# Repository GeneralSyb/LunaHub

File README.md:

# LunaHub
Astronomy power and USB hub, in development.

For now just work in progress design files for the USB hub PCB. On top of this will come the power supply PCB that has a number of buck converters to power the USB hub and a handfull of barrel jacks. I chose to keep these two boards seperate so that I don't need to worry too much about keeping one PCB small and so that I can build and test them indepentendly. To provide power to the USB hub the PSU board has a 1.1V and a 3.3V buck converter which can supply enough current to power all the electronics. The example design from TI for the TUSB8041 USB 3.1 hub IC show the usage of load switches which are controller by the IC to switch the maximum current as requested by the connected device. However to save on cost and to allow "dumb" devices to draw a lot of current, I didn't do this and connected the USB 5V power pins directly to the buck converters on the PSU board. Of course with a poly fuse chosen to allow a maximum current of 1.5A per port.

I chose to use the TUSB8041 hub IC because it was cheap, provides a lot of automatic features and seemed easy enough to use in a DIY USB hub, given my experience (which honestly isn't a whole lot).
For configuration of the IC there are a number for pins that are pulled either high or low with a resistor, and the rest is done by programming the I2C EEPROM IC. This storage chip can be programmed by removing the jumpers and connecting GND, 3.3V, SDA and SCL to an external microcontroller. The minimum amount of EEPROM storage required by the TUSB8041 is 2kB, so the 4kB EEPROM IC that I chose should be plenty.

All the differential pair lines and vias should have an impedance of 90 Ohms with a tolerance of 5% and the superspeed lines have their length matched as best as possible. The highspeed lines are mostly the same, except for the upstream port where the placement of the pins on the connector made the length matching really hard. This has been calculated using the Saturn PCB toolkit with a dielectric constant of 4.1 and a prepreg thickness on the 0.0994mm. (more details about the JLC04161H-3313 stackup can be found on [JLCPCB's](https://jlcpcb.com/impedance) website)

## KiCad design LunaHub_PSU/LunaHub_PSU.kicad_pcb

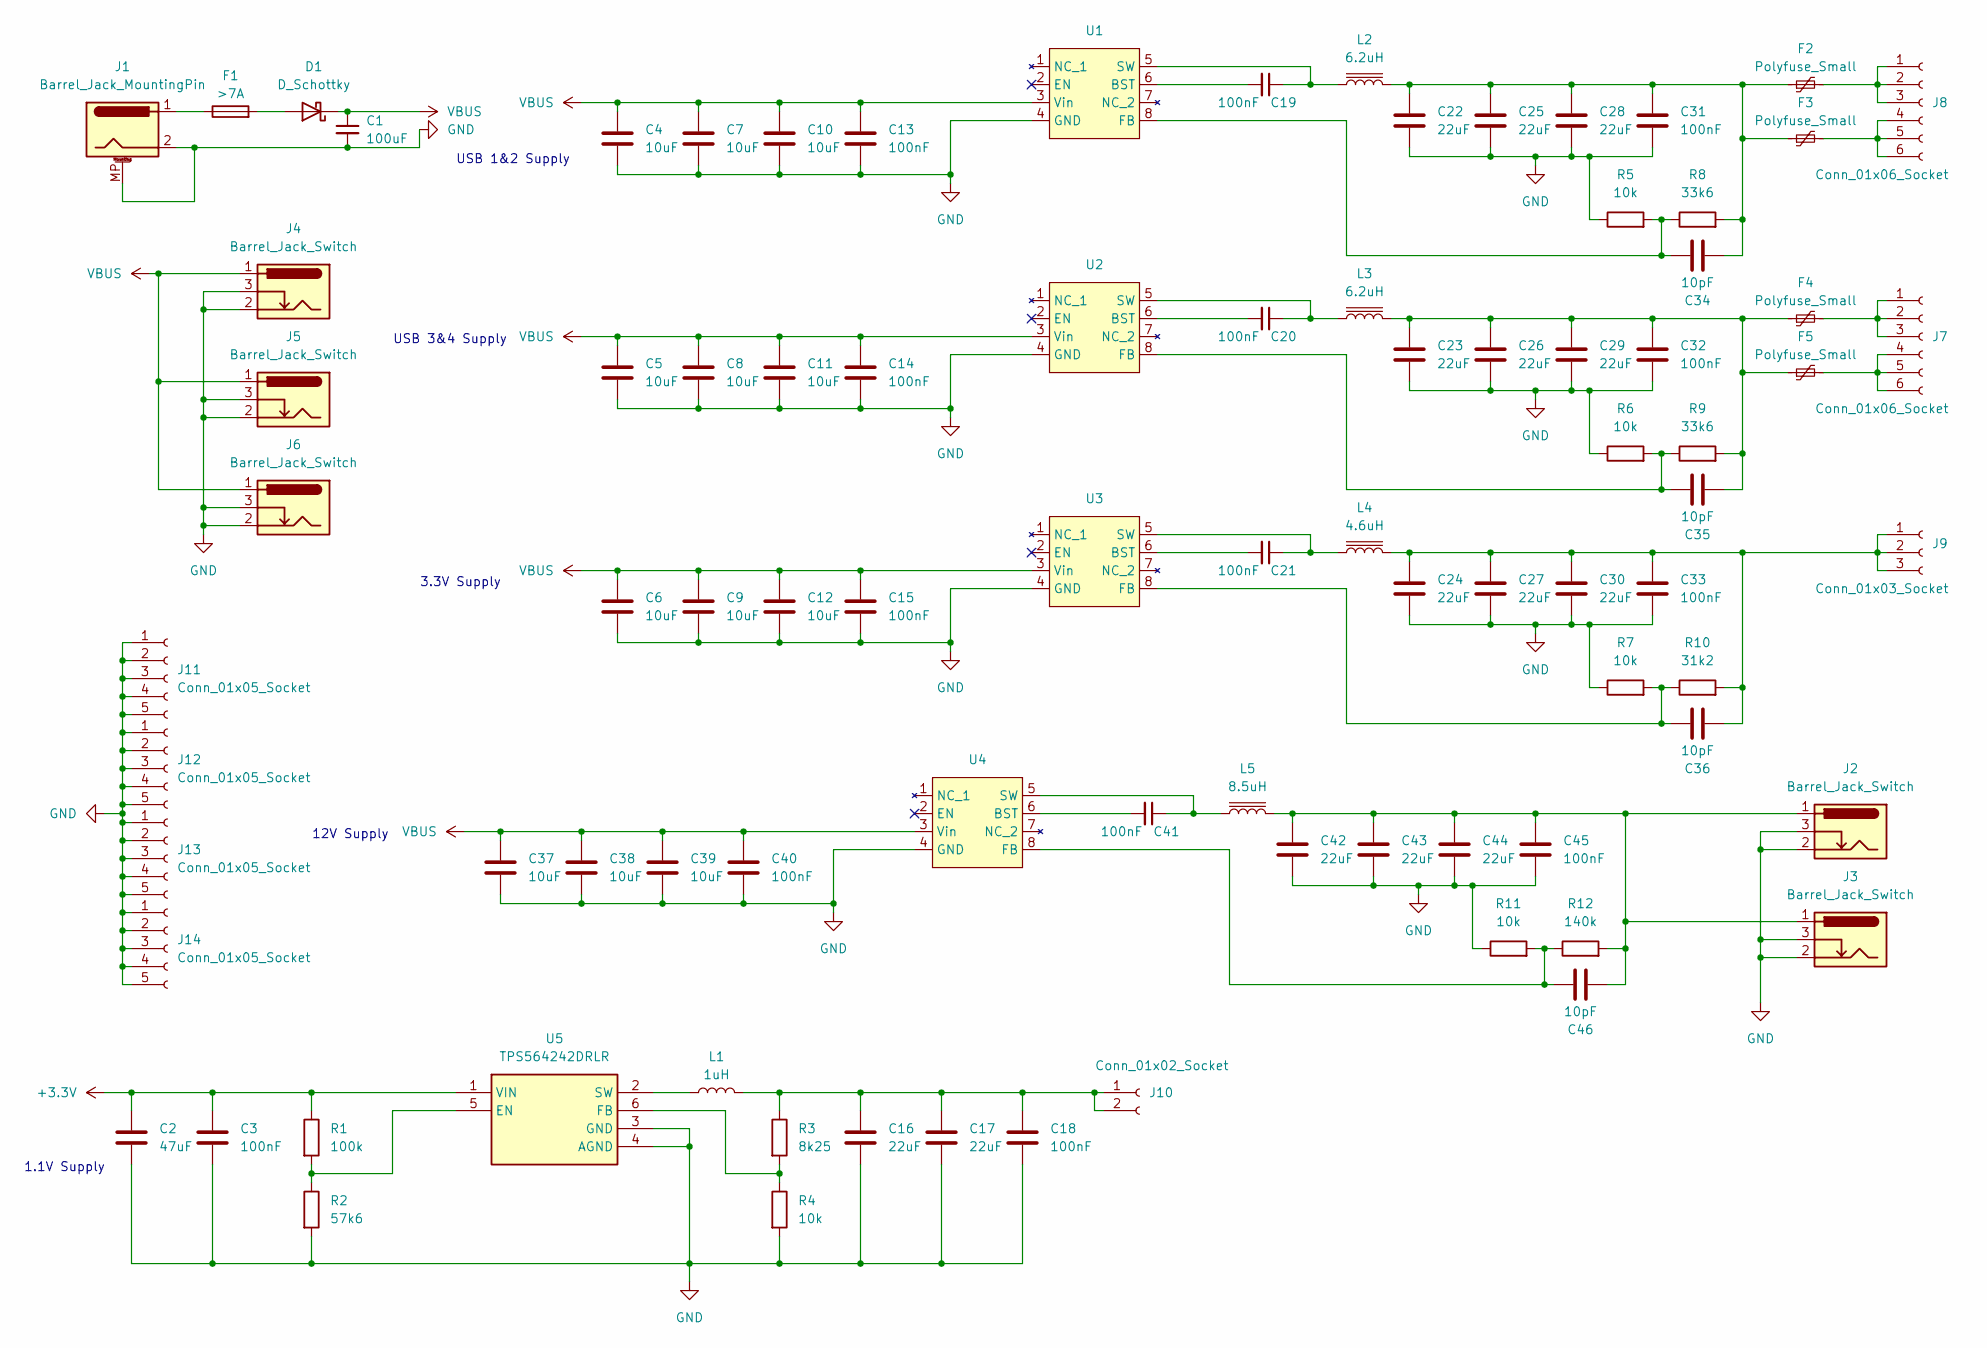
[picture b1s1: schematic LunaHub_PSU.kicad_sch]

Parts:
C1: 100uF; CP_Radial_D10.0mm_P2.50mm_P5.00mm
C2: 47uF; C_1210_3225Metric
C3, C13, C14, C15, C18, C19, C20, C21, C31, C32, C33, C40, C41, C45: 100nF; C_0805_2012Metric
C4, C5, C6, C7, C8, C9, C10, C11, C12, C37, C38, C39: 10uF; C_0805_2012Metric
C16, C17, C22, C23, C24, C25, C26, C27, C28, C29, C30, C42, C43, C44: 22uF; C_1210_3225Metric
C34, C35, C36, C46: 10pF; C_0402_1005Metric
D1: D_Schottky; D_PowerDI-5
F1: >7A; Fuseholder_Cylinder-5x20mm_Schurter_0031_8201_Horizontal_Op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
F2: Polyfuse_Small; Fuse_1206_3216Metric
F3, F4, F5: Polyfuse_Small; Fuse_0805_2012Metric
J1: Barrel_Jack_MountingPin; PJ082BH
J2, J3, J4, J5, J6: Barrel_Jack_Switch; BarrelJack_Wuerth_6941xx301002
J7, J8: Conn_01x06_Socket; PinHeader_1x06_P2.54mm_Vertical
J9: Conn_01x03_Socket; PinHeader_1x03_P2.54mm_Vertical
J10: Conn_01x02_Socket; PinHeader_1x02_P2.54mm_Vertical
J11, J12, J13, J14: Conn_01x05_Socket; PinHeader_1x05_P2.54mm_Vertical
L1: 1uH; L_1008_2520Metric
L2, L3: 6.2uH; L_Bourns_SRP7028A_7.3x6.6mm
L4: 4.6uH; L_Bourns_SRP7028A_7.3x6.6mm
L5: 8.5uH; L_Bourns_SRP7028A_7.3x6.6mm
R1: 100k; R_0805_2012Metric
R2: 57k6; R_0805_2012Metric
R3: 8k25; R_0805_2012Metric
R4: 10k; R_0805_2012Metric
R5, R6, R7, R11: 10k; R_0603_1608Metric
R8, R9: 33k6; R_0603_1608Metric
R10: 31k2; R_0603_1608Metric
R12: 140k; R_0603_1608Metric
U1, U2, U3, U4: SOT-583-8
U5: TPS564242DRLR; SOTFL50P160X60-6N; Mouser Part Number 595-TPS564242DRLR

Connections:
+3.3V: C2.1, C3.1, R1.1, U5.1 (VIN)
GND: C1.2, C2.2, C3.2, C4.2, C5.2, C6.2, C7.2, C8.2, C9.2, C10.2, C11.2, C12.2, C13.2, C14.2, C15.2, C16.2, C17.2, C18.2, C22.2, C23.2, C24.2, C25.2, C26.2, C27.2, C28.2, C29.2, C30.2, C31.2, C32.2, C33.2, C37.2, C38.2, C39.2, C40.2, C42.2, C43.2, C44.2, C45.2, J1.2, J1.MP (MountPin), J2.2, J2.3, J3.2, J3.3, J4.2, J4.3, J5.2, J5.3, J6.2, J6.3, J11.1, J11.2, J11.3, J11.4, J11.5, J12.1, J12.2, J12.3, J12.4, J12.5, J13.1, J13.2, J13.3, J13.4, J13.5, J14.1, J14.2, J14.3, J14.4, J14.5, R2.2, R4.2, R5.1, R6.1, R7.1, R11.1, U1.4 (GND), U2.4 (GND), U3.4 (GND), U4.4 (GND), U5.3 (GND), U5.4 (AGND)
unnamed: C22.1, C25.1, C28.1, C31.1, C34.2, F2.1, F3.1, L2.2, R8.2
unnamed: C23.1, C26.1, C29.1, C32.1, C35.2, F4.1, F5.1, L3.2, R9.2
unnamed: C42.1, C43.1, C44.1, C45.1, C46.2, J2.1, J3.1, L5.2, R12.2
unnamed: D1.2 (A), F1.2
unnamed: F1.1, J1.1
unnamed: F4.2, J7.1, J7.2, J7.3
unnamed: F5.2, J7.4, J7.5, J7.6
unnamed: F2.2, J8.1, J8.2, J8.3
unnamed: F3.2, J8.4, J8.5, J8.6
unnamed: C24.1, C27.1, C30.1, C33.1, C36.2, J9.1, J9.2, J9.3, L4.2, R10.2
unnamed: C16.1, C17.1, C18.1, J10.1, J10.2, L1.2, R3.1
unnamed: C19.2, U1.6 (BST)
unnamed: C34.1, R5.2, R8.1, U1.8 (FB)
unnamed: C19.1, L2.1, U1.5 (SW)
unnamed: C20.2, U2.6 (BST)
unnamed: C35.1, R6.2, R9.1, U2.8 (FB)
unnamed: C20.1, L3.1, U2.5 (SW)
unnamed: C21.2, U3.6 (BST)
unnamed: C36.1, R7.2, R10.1, U3.8 (FB)
unnamed: C21.1, L4.1, U3.5 (SW)
unnamed: C41.2, U4.6 (BST)
unnamed: C46.1, R11.2, R12.1, U4.8 (FB)
unnamed: C41.1, L5.1, U4.5 (SW)
unnamed: R1.2, R2.1, U5.5 (EN)
unnamed: R3.2, R4.1, U5.6 (FB)
unnamed: L1.1, U5.2 (SW)
VBUS: C1.1, C4.1, C5.1, C6.1, C7.1, C8.1, C9.1, C10.1, C11.1, C12.1, C13.1, C14.1, C15.1, C37.1, C38.1, C39.1, C40.1, D1.1 (K), J4.1, J5.1, J6.1, U1.3 (Vin), U2.3 (Vin), U3.3 (Vin), U4.3 (Vin)

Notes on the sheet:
USB 1&2 Supply
1.1V Supply
3.3V Supply
12V Supply
USB 3&4 Supply

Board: 2 copper layers, 88 parts (0 on the bottom side), 29 nets, no tracks yet.

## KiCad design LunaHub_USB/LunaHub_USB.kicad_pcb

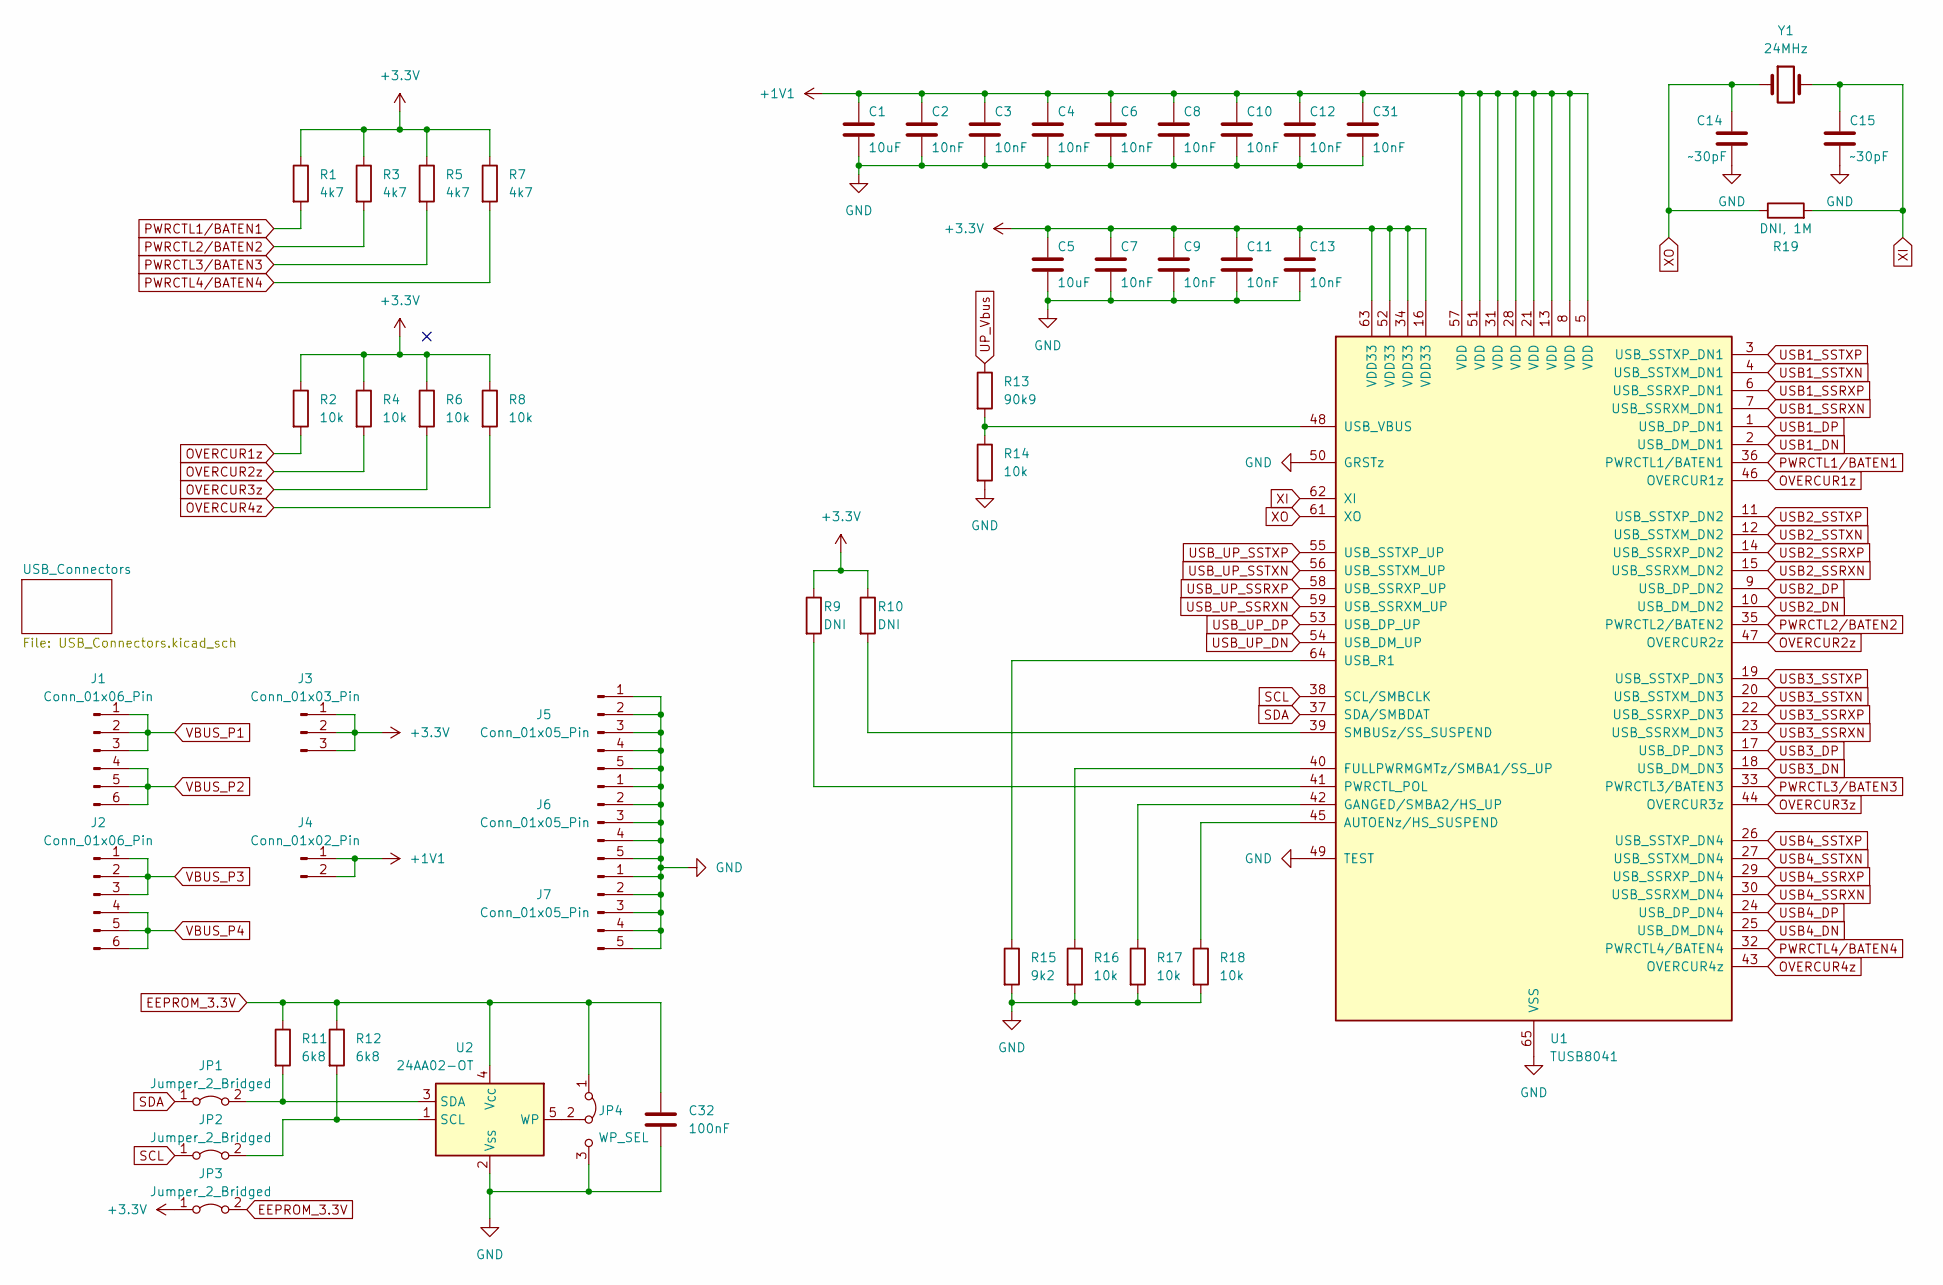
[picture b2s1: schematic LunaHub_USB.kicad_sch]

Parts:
C1, C5: 10uF; C_0805_2012Metric
C2, C3, C4, C6, C7, C8, C9, C10, C11, C12, C13, C31: 10nF; C_0402_1005Metric
C14, C15: ~30pF; C_0402_1005Metric
C32: 100nF; C_0402_1005Metric
J1, J2: Conn_01x06_Pin; PinHeader_1x06_P2.54mm_Vertical
J3: Conn_01x03_Pin; PinHeader_1x03_P2.54mm_Vertical
J4: Conn_01x02_Pin; PinHeader_1x02_P2.54mm_Vertical
J5, J6, J7: Conn_01x05_Pin; PinHeader_1x05_P2.54mm_Vertical
JP1, JP2, JP3: Jumper_2_Bridged; PinHeader_1x02_P2.54mm_Vertical
JP4: WP_SEL; PinHeader_1x03_P2.54mm_Vertical
R1, R3, R5, R7: 4k7; R_0402_1005Metric
R2, R4, R6, R8, R14, R16, R17, R18: 10k; R_0402_1005Metric
R9, R10: DNI; R_0402_1005Metric
R11, R12: 6k8; R_0402_1005Metric
R13: 90k9; R_0402_1005Metric
R15: 9k2; R_0402_1005Metric
R19: DNI, 1M; R_0402_1005Metric
U1: TUSB8041; QFN-64-1EP_9x9mm_P0.5mm_EP6x6mm_ThermalVias
U2: 24AA02-OT; SOT-23-5
Y1: 24MHz; Crystal_HC49-4H_Vertical

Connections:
+1V1: C1.1, C2.1, C3.1, C4.1, C6.1, C8.1, C10.1, C12.1, C31.1, J4.1, J4.2, U1.5 (VDD), U1.8 (VDD), U1.13 (VDD), U1.21 (VDD), U1.28 (VDD), U1.31 (VDD), U1.51 (VDD), U1.57 (VDD)
+3.3V: C5.1, C7.1, C9.1, C11.1, C13.1, J3.1, J3.2, J3.3, JP3.1 (A), R1.1, R2.1, R3.1, R4.1, R5.1, R6.1, R7.1, R8.1, R9.1, R10.1, U1.16 (VDD33), U1.34 (VDD33), U1.52 (VDD33), U1.63 (VDD33)
EEPROM_3.3V: C32.1, JP3.2 (B), JP4.1 (A), R11.1, R12.1, U2.4 (V_{CC})
GND: C1.2, C2.2, C3.2, C4.2, C5.2, C6.2, C7.2, C8.2, C9.2, C10.2, C11.2, C12.2, C13.2, C14.2, C15.2, C31.2, C32.2, J5.1, J5.2, J5.3, J5.4, J5.5, J6.1, J6.2, J6.3, J6.4, J6.5, J7.1, J7.2, J7.3, J7.4, J7.5, JP4.3 (B), R14.2, R15.2, R16.2, R17.2, R18.2, U1.49 (TEST), U1.50 (GRSTz), U1.65 (VSS), U2.2 (V_{SS}); also elsewhere on the board
unnamed: JP1.2 (B), R11.2, U2.3 (SDA)
unnamed: JP2.2 (B), R12.2, U2.1 (SCL)
unnamed: JP4.2 (C), U2.5 (WP)
unnamed: R18.1, U1.45 (AUTOENz/HS_SUSPEND)
unnamed: R16.1, U1.40 (FULLPWRMGMTz/SMBA1/SS_UP)
unnamed: R17.1, U1.42 (GANGED/SMBA2/HS_UP)
unnamed: R9.2, U1.41 (PWRCTL_POL)
unnamed: R10.2, U1.39 (SMBUSz/SS_SUSPEND)
unnamed: R15.1, U1.64 (USB_R1)
unnamed: R13.2, R14.1, U1.48 (USB_VBUS)
OVERCUR1z: R2.2, U1.46 (OVERCUR1z)
OVERCUR2z: R4.2, U1.47 (OVERCUR2z)
OVERCUR3z: R6.2, U1.44 (OVERCUR3z)
OVERCUR4z: R8.2, U1.43 (OVERCUR4z)
PWRCTL1/BATEN1: R1.2, U1.36 (PWRCTL1/BATEN1)
PWRCTL2/BATEN2: R3.2, U1.35 (PWRCTL2/BATEN2)
PWRCTL3/BATEN3: R5.2, U1.33 (PWRCTL3/BATEN3)
PWRCTL4/BATEN4: R7.2, U1.32 (PWRCTL4/BATEN4)
SCL: JP2.1 (A), U1.38 (SCL/SMBCLK)
SDA: JP1.1 (A), U1.37 (SDA/SMBDAT)
UP_Vbus: R13.1; also elsewhere on the board
USB1_DN: U1.2 (USB_DM_DN1); also elsewhere on the board
USB1_DP: U1.1 (USB_DP_DN1); also elsewhere on the board
USB1_SSRXN: U1.7 (USB_SSRXM_DN1); also elsewhere on the board
USB1_SSRXP: U1.6 (USB_SSRXP_DN1); also elsewhere on the board
USB1_SSTXN: U1.4 (USB_SSTXM_DN1); also elsewhere on the board
USB1_SSTXP: U1.3 (USB_SSTXP_DN1); also elsewhere on the board
USB2_DN: U1.10 (USB_DM_DN2); also elsewhere on the board
USB2_DP: U1.9 (USB_DP_DN2); also elsewhere on the board
USB2_SSRXN: U1.15 (USB_SSRXM_DN2); also elsewhere on the board
USB2_SSRXP: U1.14 (USB_SSRXP_DN2); also elsewhere on the board
USB2_SSTXN: U1.12 (USB_SSTXM_DN2); also elsewhere on the board
USB2_SSTXP: U1.11 (USB_SSTXP_DN2); also elsewhere on the board
USB3_DN: U1.18 (USB_DM_DN3); also elsewhere on the board
USB3_DP: U1.17 (USB_DP_DN3); also elsewhere on the board
USB3_SSRXN: U1.23 (USB_SSRXM_DN3); also elsewhere on the board
USB3_SSRXP: U1.22 (USB_SSRXP_DN3); also elsewhere on the board
USB3_SSTXN: U1.20 (USB_SSTXM_DN3); also elsewhere on the board
USB3_SSTXP: U1.19 (USB_SSTXP_DN3); also elsewhere on the board
USB4_DN: U1.25 (USB_DM_DN4); also elsewhere on the board
USB4_DP: U1.24 (USB_DP_DN4); also elsewhere on the board
USB4_SSRXN: U1.30 (USB_SSRXM_DN4); also elsewhere on the board
USB4_SSRXP: U1.29 (USB_SSRXP_DN4); also elsewhere on the board
USB4_SSTXN: U1.27 (USB_SSTXM_DN4); also elsewhere on the board
USB4_SSTXP: U1.26 (USB_SSTXP_DN4); also elsewhere on the board
USB_UP_DN: U1.54 (USB_DM_UP); also elsewhere on the board
USB_UP_DP: U1.53 (USB_DP_UP); also elsewhere on the board
USB_UP_SSRXN: U1.59 (USB_SSRXM_UP); also elsewhere on the board
USB_UP_SSRXP: U1.58 (USB_SSRXP_UP); also elsewhere on the board
USB_UP_SSTXN: U1.56 (USB_SSTXM_UP); also elsewhere on the board
USB_UP_SSTXP: U1.55 (USB_SSTXP_UP); also elsewhere on the board
VBUS_P1: J1.1, J1.2, J1.3; also elsewhere on the board
VBUS_P2: J1.4, J1.5, J1.6; also elsewhere on the board
VBUS_P3: J2.1, J2.2, J2.3; also elsewhere on the board
VBUS_P4: J2.4, J2.5, J2.6; also elsewhere on the board
XI: C15.1, R19.2, U1.62 (XI), Y1.2
XO: C14.1, R19.1, U1.61 (XO), Y1.1

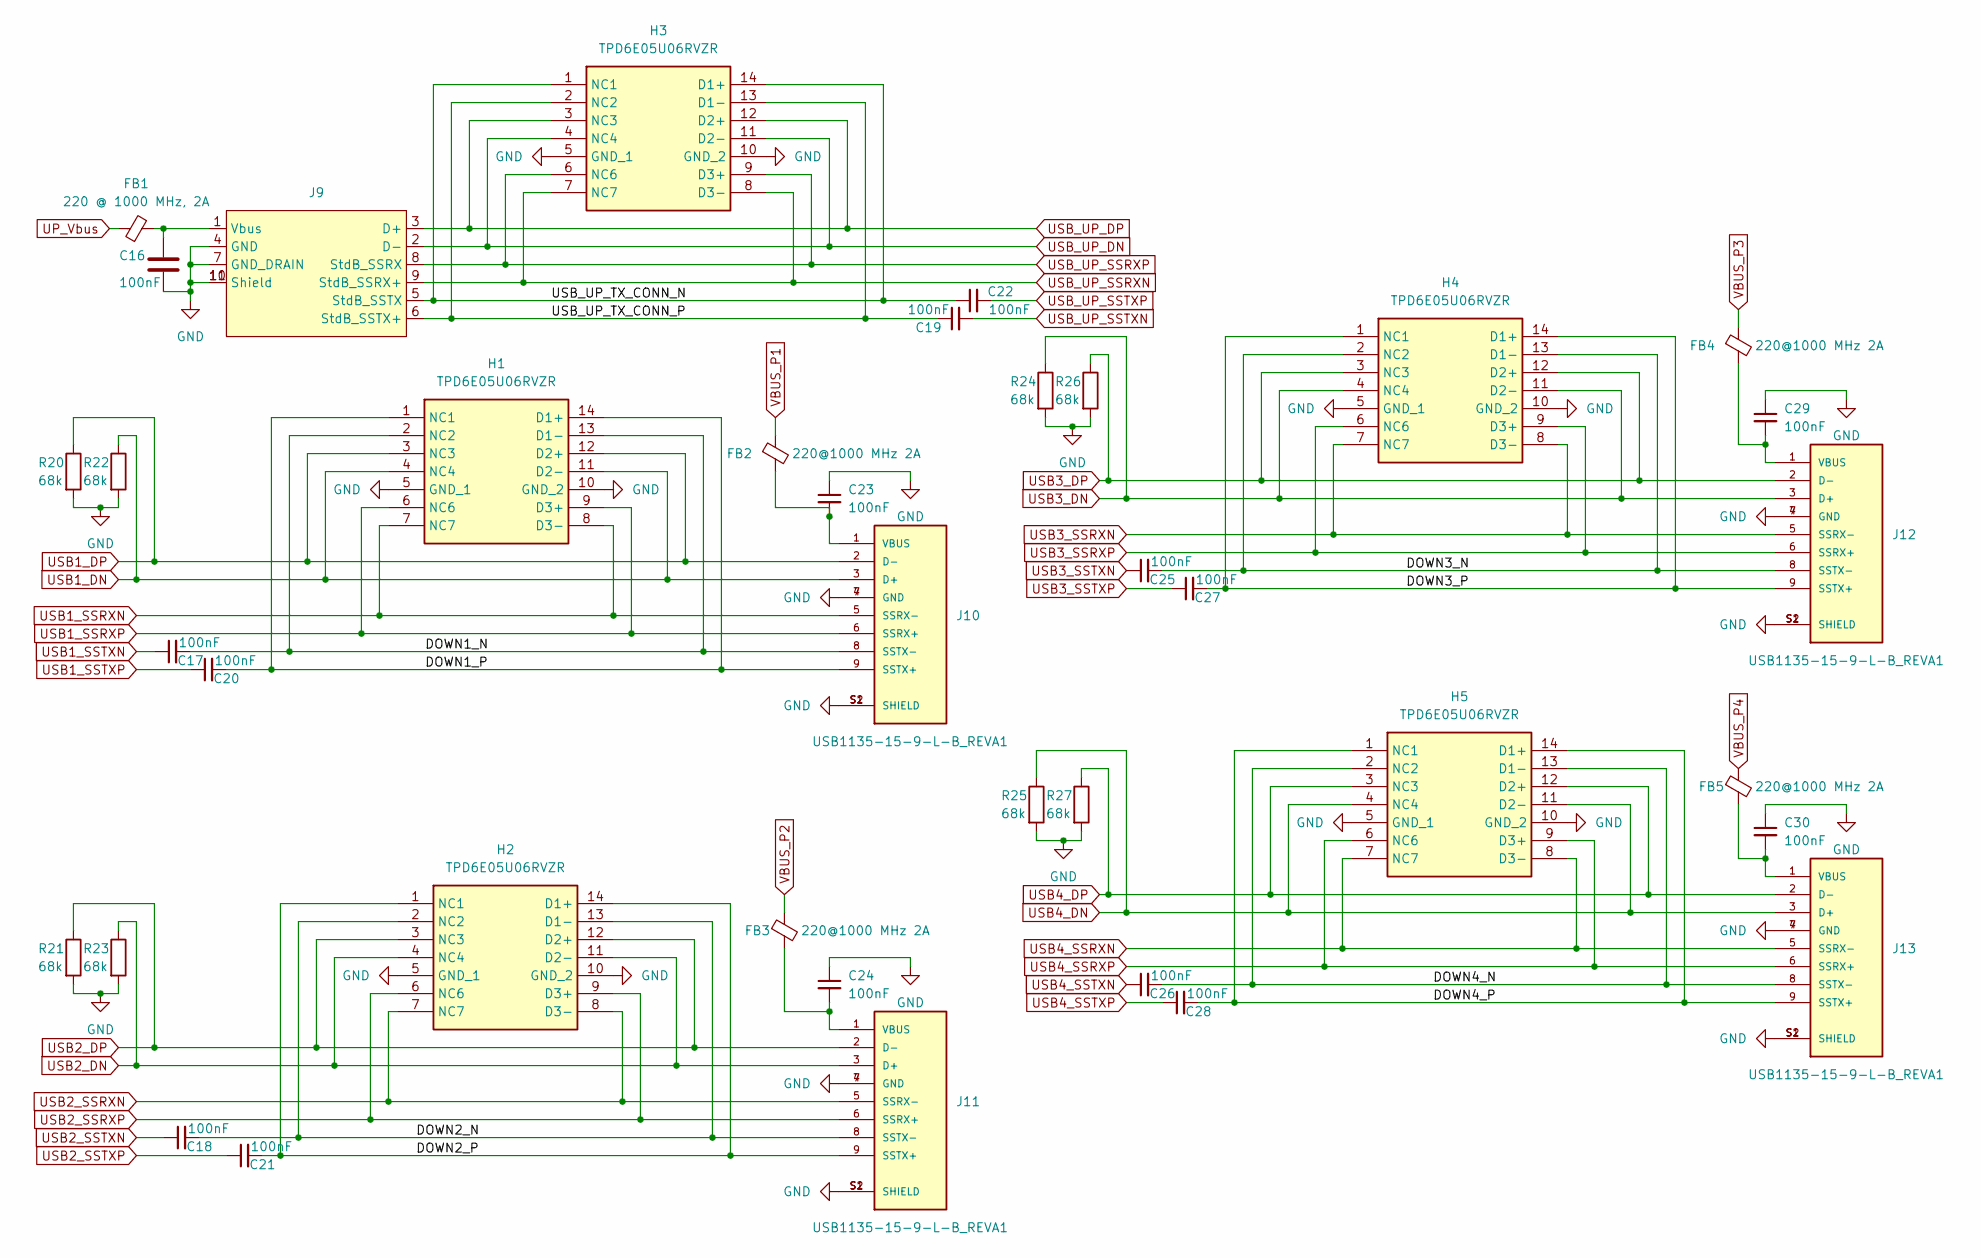
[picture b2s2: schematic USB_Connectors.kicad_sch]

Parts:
C16, C17, C18, C19, C20, C21, C22, C23, C24, C25, C26, C27, C28, C29, C30: 100nF; C_0402_1005Metric
FB1: 220 @ 1000 MHz, 2A; R_1206_3216Metric
FB2, FB3, FB4, FB5: 220@1000 MHz 2A; R_1206_3216Metric
H1, H2, H3, H4, H5: TPD6E05U06RVZR; SON50P135X350X55-14N; Mouser Part Number 595-TPD6E05U06RVZR
J9: WR-COM_USB_TYPE_B
J10, J11, J12, J13: USB1135-15-9-L-B_REVA1; GCT_USB1135-15-9-L-B_REVA1; PARTREV A1; DigiKey_Part_Number 2073-USB1135-15-9-L-B-ND
R20, R21, R22, R23, R24, R25, R26, R27: 68k; R_0402_1005Metric

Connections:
/USB_Connectors/DOWN1_N: C17.2, H1.2 (NC2), H1.13 (D1-), J10.8 (SSTX-)
/USB_Connectors/DOWN1_P: C20.2, H1.1 (NC1), H1.14 (D1+), J10.9 (SSTX+)
/USB_Connectors/DOWN2_N: C18.2, H2.2 (NC2), H2.13 (D1-), J11.8 (SSTX-)
/USB_Connectors/DOWN2_P: C21.2, H2.1 (NC1), H2.14 (D1+), J11.9 (SSTX+)
/USB_Connectors/DOWN3_N: C25.2, H4.2 (NC2), H4.13 (D1-), J12.8 (SSTX-)
/USB_Connectors/DOWN3_P: C27.2, H4.1 (NC1), H4.14 (D1+), J12.9 (SSTX+)
/USB_Connectors/DOWN4_N: C26.2, H5.2 (NC2), H5.13 (D1-), J13.8 (SSTX-)
/USB_Connectors/DOWN4_P: C28.2, H5.1 (NC1), H5.14 (D1+), J13.9 (SSTX+)
/USB_Connectors/USB_UP_TX_CONN_N: C22.1, H3.1 (NC1), H3.14 (D1+), J9.5 (StdB_SSTX)
/USB_Connectors/USB_UP_TX_CONN_P: C19.1, H3.2 (NC2), H3.13 (D1-), J9.6 (StdB_SSTX+)
GND: C16.2, C23.1, C24.1, C29.1, C30.1, H1.5 (GND_1), H1.10 (GND_2), H2.5 (GND_1), H2.10 (GND_2), H3.5 (GND_1), H3.10 (GND_2), H4.5 (GND_1), H4.10 (GND_2), H5.5 (GND_1), H5.10 (GND_2), J9.4 (GND), J9.7 (GND_DRAIN), J9.10 (Shield), J9.11 (Shield), J10.4 (GND), J10.7 (GND), J10.S1 (SHIELD), J10.S2 (SHIELD), J11.4 (GND), J11.7 (GND), J11.S1 (SHIELD), J11.S2 (SHIELD), J12.4 (GND), J12.7 (GND), J12.S1 (SHIELD), J12.S2 (SHIELD), J13.4 (GND), J13.7 (GND), J13.S1 (SHIELD), J13.S2 (SHIELD), R20.2, R21.2, R22.2, R23.2, R24.2, R25.2, R26.2, R27.2; also elsewhere on the board
unnamed: C16.1, FB1.2, J9.1 (Vbus)
unnamed: C23.2, FB2.2, J10.1 (VBUS)
unnamed: C24.2, FB3.2, J11.1 (VBUS)
unnamed: C29.2, FB4.2, J12.1 (VBUS)
unnamed: C30.2, FB5.2, J13.1 (VBUS)
UP_Vbus: FB1.1; also elsewhere on the board
USB1_DN: H1.4 (NC4), H1.11 (D2-), J10.3 (D+), R22.1; also elsewhere on the board
USB1_DP: H1.3 (NC3), H1.12 (D2+), J10.2 (D-), R20.1; also elsewhere on the board
USB1_SSRXN: H1.7 (NC7), H1.8 (D3-), J10.5 (SSRX-); also elsewhere on the board
USB1_SSRXP: H1.6 (NC6), H1.9 (D3+), J10.6 (SSRX+); also elsewhere on the board
USB1_SSTXN: C17.1; also elsewhere on the board
USB1_SSTXP: C20.1; also elsewhere on the board
USB2_DN: H2.4 (NC4), H2.11 (D2-), J11.3 (D+), R23.1; also elsewhere on the board
USB2_DP: H2.3 (NC3), H2.12 (D2+), J11.2 (D-), R21.1; also elsewhere on the board
USB2_SSRXN: H2.7 (NC7), H2.8 (D3-), J11.5 (SSRX-); also elsewhere on the board
USB2_SSRXP: H2.6 (NC6), H2.9 (D3+), J11.6 (SSRX+); also elsewhere on the board
USB2_SSTXN: C18.1; also elsewhere on the board
USB2_SSTXP: C21.1; also elsewhere on the board
USB3_DN: H4.4 (NC4), H4.11 (D2-), J12.3 (D+), R24.1; also elsewhere on the board
USB3_DP: H4.3 (NC3), H4.12 (D2+), J12.2 (D-), R26.1; also elsewhere on the board
USB3_SSRXN: H4.7 (NC7), H4.8 (D3-), J12.5 (SSRX-); also elsewhere on the board
USB3_SSRXP: H4.6 (NC6), H4.9 (D3+), J12.6 (SSRX+); also elsewhere on the board
USB3_SSTXN: C25.1; also elsewhere on the board
USB3_SSTXP: C27.1; also elsewhere on the board
USB4_DN: H5.4 (NC4), H5.11 (D2-), J13.3 (D+), R25.1; also elsewhere on the board
USB4_DP: H5.3 (NC3), H5.12 (D2+), J13.2 (D-), R27.1; also elsewhere on the board
USB4_SSRXN: H5.7 (NC7), H5.8 (D3-), J13.5 (SSRX-); also elsewhere on the board
USB4_SSRXP: H5.6 (NC6), H5.9 (D3+), J13.6 (SSRX+); also elsewhere on the board
USB4_SSTXN: C26.1; also elsewhere on the board
USB4_SSTXP: C28.1; also elsewhere on the board
USB_UP_DN: H3.4 (NC4), H3.11 (D2-), J9.2 (D-); also elsewhere on the board
USB_UP_DP: H3.3 (NC3), H3.12 (D2+), J9.3 (D+); also elsewhere on the board
USB_UP_SSRXN: H3.7 (NC7), H3.8 (D3-), J9.9 (StdB_SSRX+); also elsewhere on the board
USB_UP_SSRXP: H3.6 (NC6), H3.9 (D3+), J9.8 (StdB_SSRX); also elsewhere on the board
USB_UP_SSTXN: C19.2; also elsewhere on the board
USB_UP_SSTXP: C22.2; also elsewhere on the board
VBUS_P1: FB2.1; also elsewhere on the board
VBUS_P2: FB3.1; also elsewhere on the board
VBUS_P3: FB4.1; also elsewhere on the board
VBUS_P4: FB5.1; also elsewhere on the board

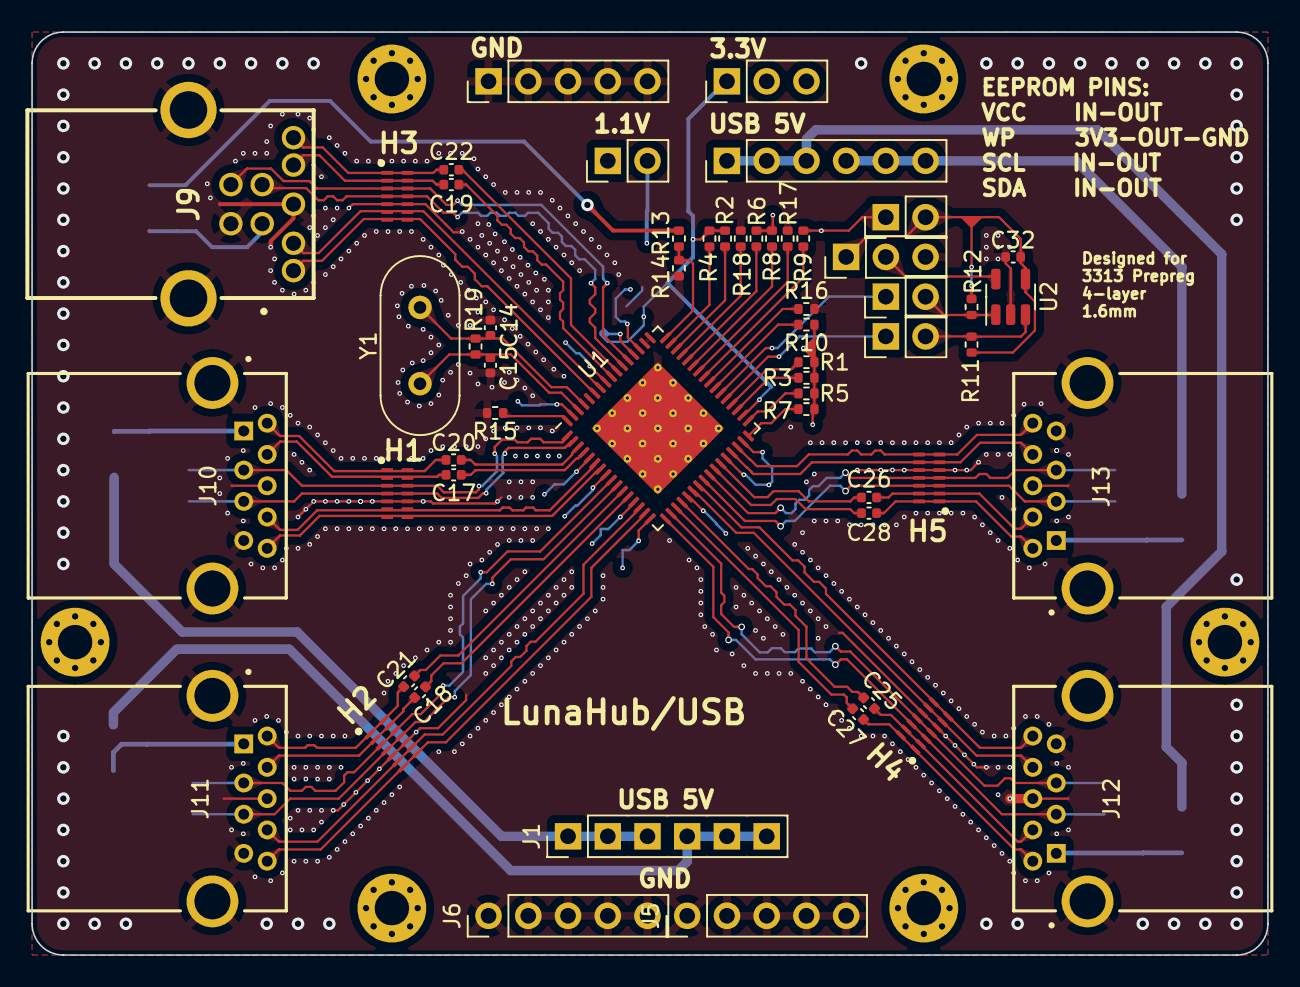
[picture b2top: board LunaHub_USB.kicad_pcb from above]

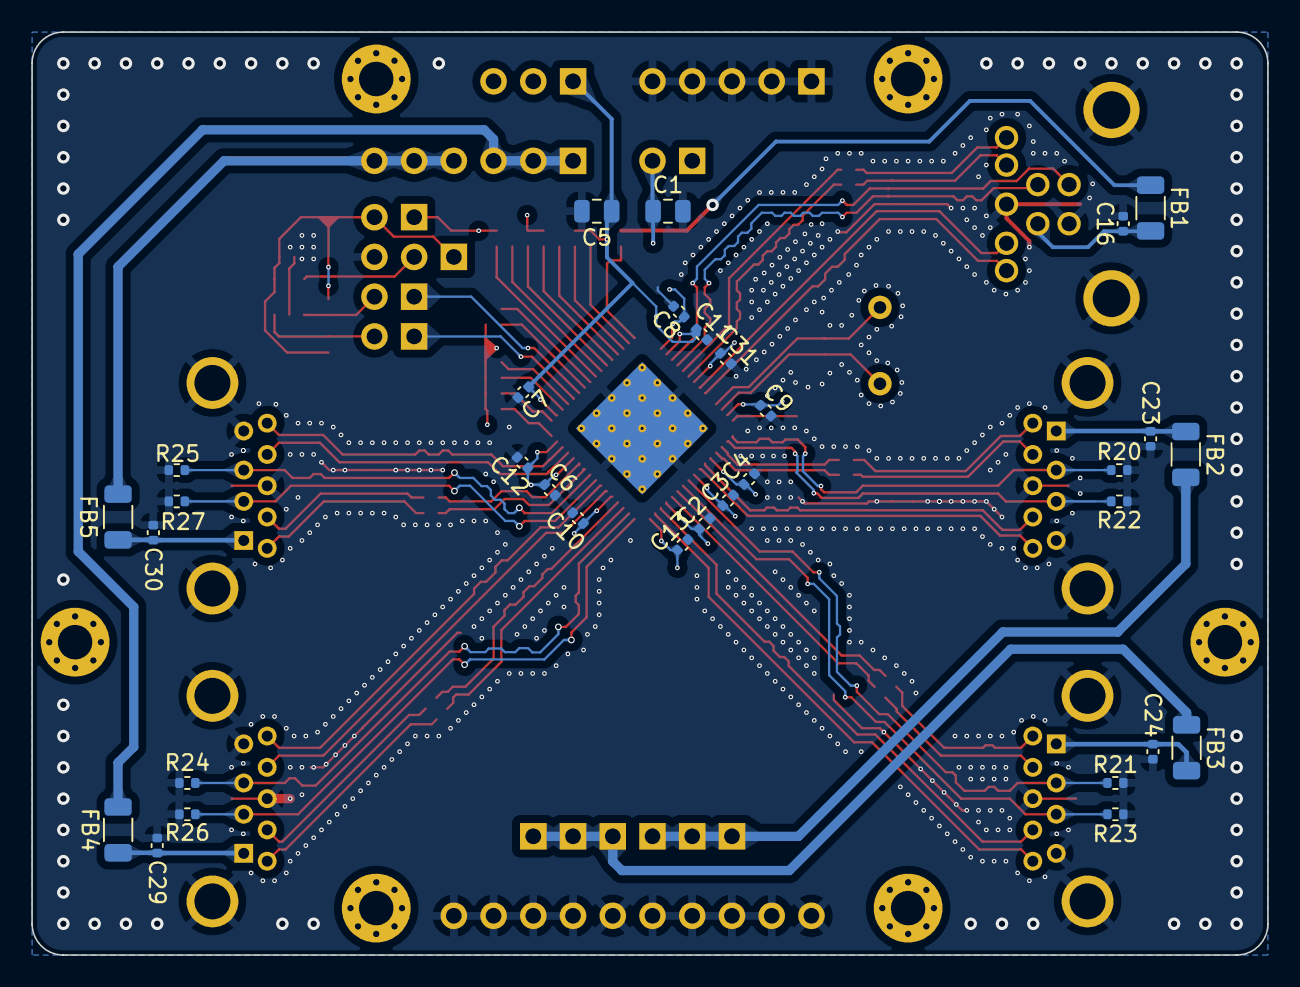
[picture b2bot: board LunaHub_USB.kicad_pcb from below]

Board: 4 copper layers, 79.0 x 59.0 mm, 88 parts (32 on the bottom side), 76 nets.

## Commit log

2024-01-30 Project file upload
